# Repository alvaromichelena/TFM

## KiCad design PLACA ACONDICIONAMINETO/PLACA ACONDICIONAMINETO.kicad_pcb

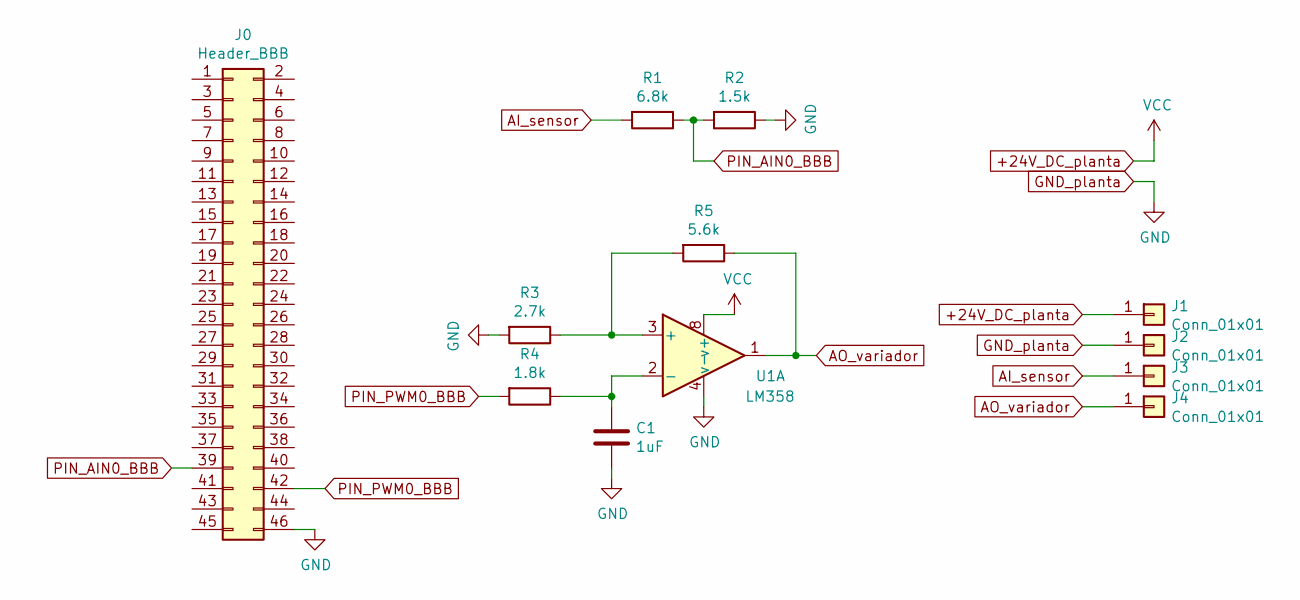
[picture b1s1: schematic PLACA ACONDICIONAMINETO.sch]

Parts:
C1: 1uF; C_Rect_L7.2mm_W4.5mm_P5.00mm_FKS2_FKP2_MKS2_MKP2
J0: Header_BBB; PinHeader_2x23_P2.54mm_Vertical
J1, J2, J3, J4: Conn_01x01; Banana_Jack_1Pin
R1: 6.8k; R_Axial_DIN0207_L6.3mm_D2.5mm_P7.62mm_Horizontal
R2: 1.5k; R_Axial_DIN0207_L6.3mm_D2.5mm_P7.62mm_Horizontal
R3: 2.7k; R_Axial_DIN0207_L6.3mm_D2.5mm_P7.62mm_Horizontal
R4: 1.8k; R_Axial_DIN0207_L6.3mm_D2.5mm_P7.62mm_Horizontal
R5: 5.6k; R_Axial_DIN0207_L6.3mm_D2.5mm_P7.62mm_Horizontal
U1: LM358; DIP-8_W7.62mm_Socket_LongPads

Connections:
+24V_DC_planta: J1.1, U1.8 (v+)
AI_sensor: J3.1, R1.2
AO_variador: J4.1, R5.1, U1.1
GND_planta: C1.2, J0.46, J2.1, R2.1, R3.2, U1.4 (v-)
unnamed: C1.1, R4.1, U1.2 (-)
unnamed: R3.1, R5.2, U1.3 (+)
PIN_AIN0_BBB: J0.39, R1.1, R2.2
PIN_PWM0_BBB: J0.42, R4.2

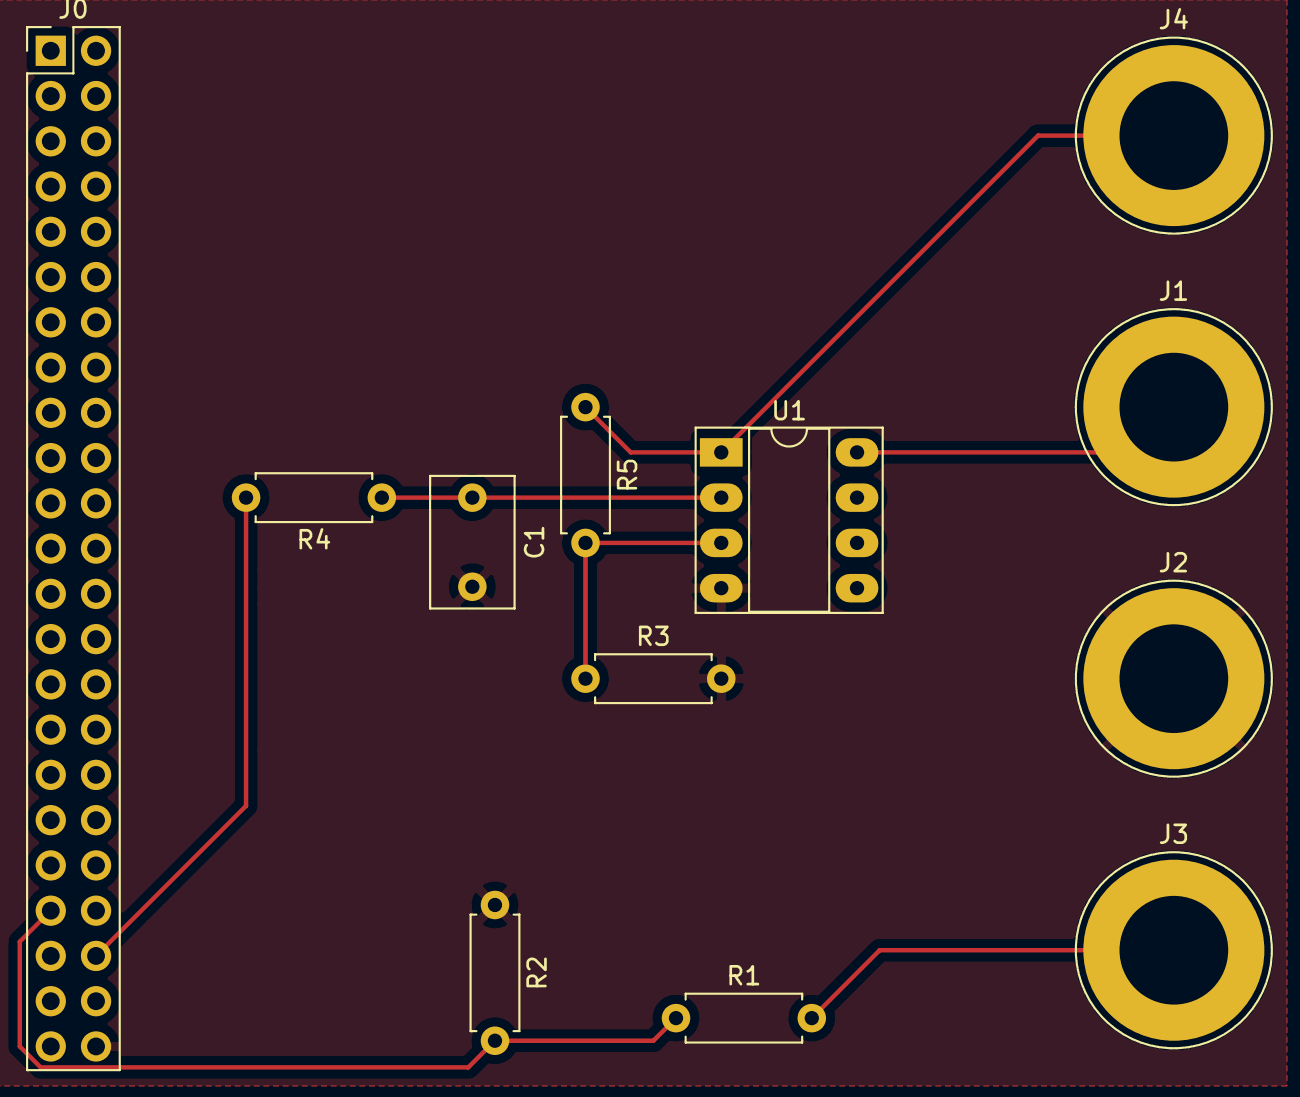
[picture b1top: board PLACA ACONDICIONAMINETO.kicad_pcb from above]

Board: 2 copper layers, 12 parts (0 on the bottom side), 8 nets.
